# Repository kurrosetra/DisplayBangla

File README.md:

# DisplayBangla
INKA - Display for Bangladesh's train

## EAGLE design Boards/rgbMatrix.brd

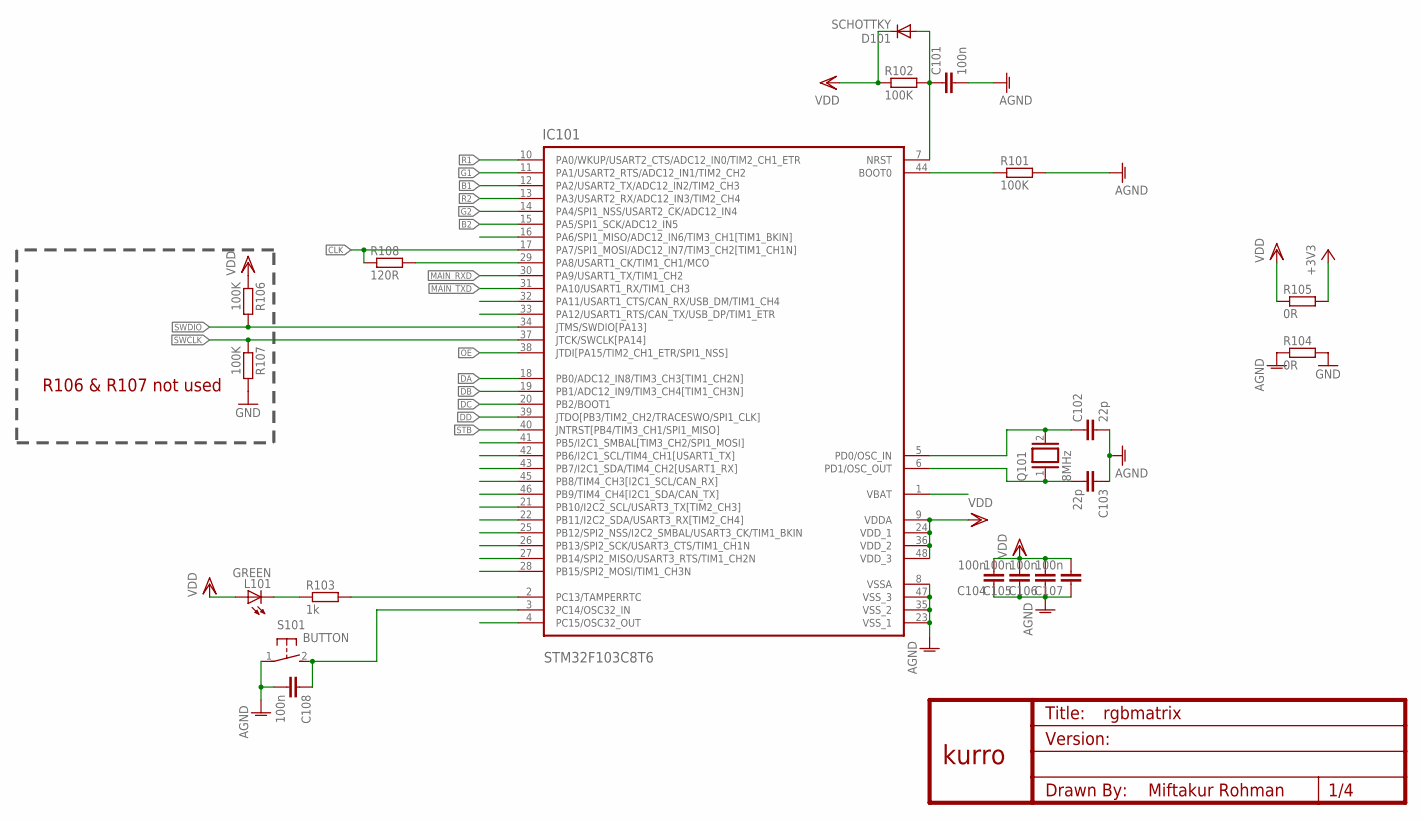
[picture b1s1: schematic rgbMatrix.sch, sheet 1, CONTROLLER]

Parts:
C101, C104, C105, C106, C107, C108: 100n; C0603
C102, C103: 22p; C0603
D101: SCHOTTKY; MICROMELF-W
IC101: STM32F103C8T6; QFP50P900X900X160-48N
L101: GREEN; LED3MM
Q101: 8MHz; QS
R101, R102, R106, R107: 100K; R0603
R103: 1k; R0603
R104, R105: 0R; R0603
R108: 120R; R0603
S101: BUTTON; B3F-01XXX
U$1: KURRO_FOOTPRINT; KURRO-LOGO

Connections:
+3V3: R105.2; also elsewhere on the board
AGND: C101.2, C102.2, C103.1, C104.1, C105.1, C106.1, C107.1, C108.2, IC101.8 (VSSA), IC101.23 (VSS_1), IC101.35 (VSS_2), IC101.47 (VSS_3), R101.2, R104.1, S101.1
B1: IC101.12 (PA2/USART2_TX/ADC12_IN2/TIM2_CH3); also elsewhere on the board
B2: IC101.15 (PA5/SPI1_SCK/ADC12_IN5); also elsewhere on the board
BOOT0: IC101.44 (BOOT0), R101.1
CLK: IC101.17 (PA7/SPI1_MOSI/ADC12_IN7/TIM3_CH2[TIM1_C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), R108.1; also elsewhere on the board
DA: IC101.18 (PB0/ADC12_IN8/TIM3_CH3[TIM1_CH2N]); also elsewhere on the board
DB: IC101.19 (PB1/ADC12_IN9/TIM3_CH4[TIM1_CH3N]); also elsewhere on the board
DC: IC101.20 (PB2/BOOT1); also elsewhere on the board
DD: IC101.39 (JTDO[PB3/TIM2_CH2/TRACESWO/SPI1_CLK]); also elsewhere on the board
G1: IC101.11 (PA1/USART2_RTS/ADC12_IN1/TIM2_CH2); also elsewhere on the board
G2: IC101.14 (PA4/SPI1_NSS/USART2_CK/ADC12_IN4); also elsewhere on the board
GND: R104.2, R107.2; also elsewhere on the board
LED1_BUILTIN: IC101.2 (PC13/TAMPERRTC), R103.2
MAIN_RXD: IC101.30 (PA9/USART1_TX/TIM1_CH2)
MAIN_TXD: IC101.31 (PA10/USART1_RX/TIM1_CH3); also elsewhere on the board
unnamed: IC101.29 (PA8/USART1_CK/TIM1_CH1/MCO), R108.2
unnamed: C103.2, IC101.6 (PD1/OSC_OUT), Q101.1
unnamed: C102.1, IC101.5 (PD0/OSC_IN), Q101.2
unnamed: L101.K (C), R103.1
unnamed: C108.1, IC101.3 (PC14/OSC32_IN), S101.2 (S)
OE: IC101.38 (JTDI[PA15/TIM2_CH1_ETR/SPI1_NSS]); also elsewhere on the board
R1: IC101.10 (PA0/WKUP/USART2_CTS/ADC12_IN0/TIM2_CH1_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); also elsewhere on the board
R2: IC101.13 (PA3/USART2_RX/ADC12_IN3/TIM2_CH4); also elsewhere on the board
RST: C101.1, D101.A, IC101.7 (NRST), R102.2
STB: IC101.40 (JNTRST[PB4/TIM3_CH1/SPI1_MISO]); also elsewhere on the board
SWCLK: IC101.37 (JTCK/SWCLK[PA14]), R107.1; also elsewhere on the board
SWDIO: IC101.34 (JTMS/SWDIO[PA13]), R106.2; also elsewhere on the board
VDD: C104.2, C105.2, C106.2, C107.2, D101.C, IC101.9 (VDDA), IC101.24 (VDD_1), IC101.36 (VDD_2), IC101.48 (VDD_3), L101.A, R102.1, R105.1, R106.1

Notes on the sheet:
R106 & R107 not used

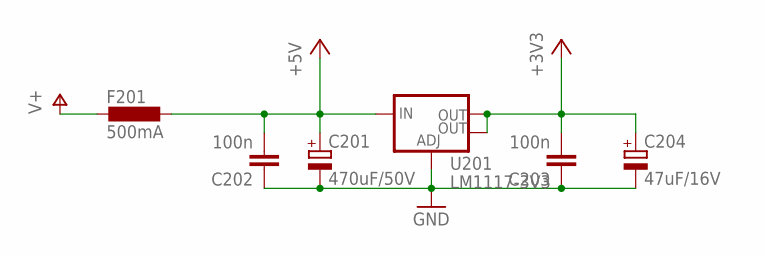
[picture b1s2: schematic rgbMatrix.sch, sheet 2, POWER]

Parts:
C201: 470uF/50V; E5-10,5
C202, C203: 100n; C0603
C204: 47uF/16V; E2-5
F201: 500mA; L1812
U201: LM1117-3V3; SOT223

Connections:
+3V3: C203.2, C204.+, U201.2 (OUT), U201.4 (OUT); also elsewhere on the board
+5V: C201.+, C202.2, F201.1, U201.3 (IN)
GND: C201.-, C202.1, C203.1, C204.-, U201.1 (ADJ); also elsewhere on the board
V+: F201.2; also elsewhere on the board

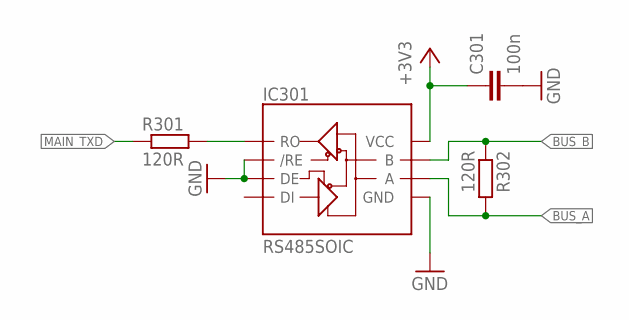
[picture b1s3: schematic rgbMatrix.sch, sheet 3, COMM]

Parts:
C301: 100n; C0603
IC301: RS485SOIC; SO08
R301, R302: 120R; R0603

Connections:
+3V3: C301.1, IC301.8 (VCC); also elsewhere on the board
BUS_A: IC301.6 (A), R302.2; also elsewhere on the board
BUS_B: IC301.7 (B), R302.1; also elsewhere on the board
GND: C301.2, IC301.2 (/RE), IC301.3 (DE), IC301.5 (GND); also elsewhere on the board
MAIN_TXD: R301.1; also elsewhere on the board
unnamed: IC301.1 (RO), R301.2

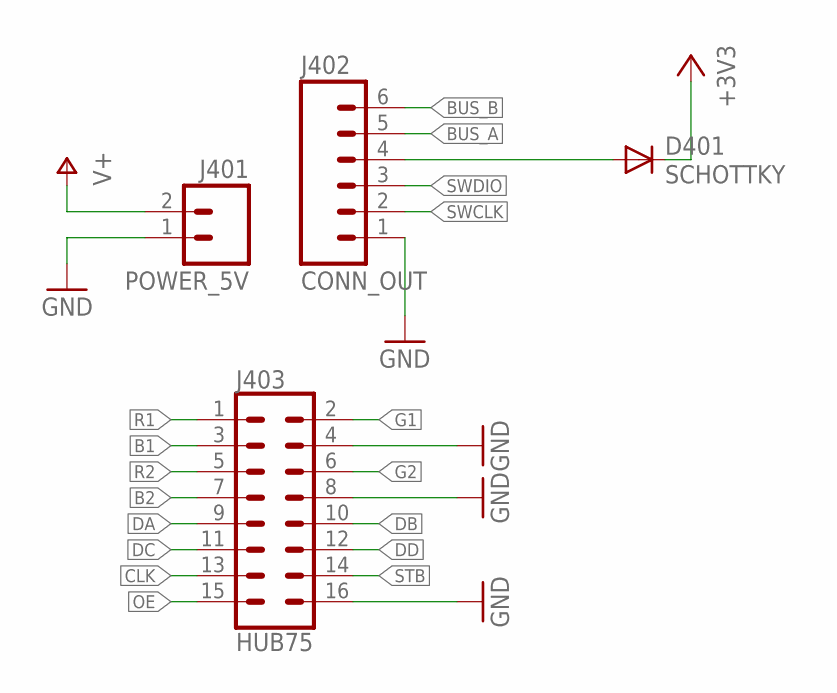
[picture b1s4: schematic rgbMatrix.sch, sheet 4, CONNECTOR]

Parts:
D401: SCHOTTKY; MICROMELF-W
J401: POWER_5V; XH-2-RA
J402: CONN_OUT; XH-6-RA
J403: HUB75; 2X08-LOCK

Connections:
+3V3: D401.C; also elsewhere on the board
B1: J403.3; also elsewhere on the board
B2: J403.7; also elsewhere on the board
BUS_A: J402.5; also elsewhere on the board
BUS_B: J402.6; also elsewhere on the board
CLK: J403.13; also elsewhere on the board
DA: J403.9; also elsewhere on the board
DB: J403.10; also elsewhere on the board
DC: J403.11; also elsewhere on the board
DD: J403.12; also elsewhere on the board
G1: J403.2; also elsewhere on the board
G2: J403.6; also elsewhere on the board
GND: J401.1, J402.1, J403.4, J403.8, J403.16; also elsewhere on the board
unnamed: D401.A, J402.4
OE: J403.15; also elsewhere on the board
R1: J403.1; also elsewhere on the board
R2: J403.5; also elsewhere on the board
STB: J403.14; also elsewhere on the board
SWCLK: J402.2; also elsewhere on the board
SWDIO: J402.3; also elsewhere on the board
V+: J401.2; also elsewhere on the board

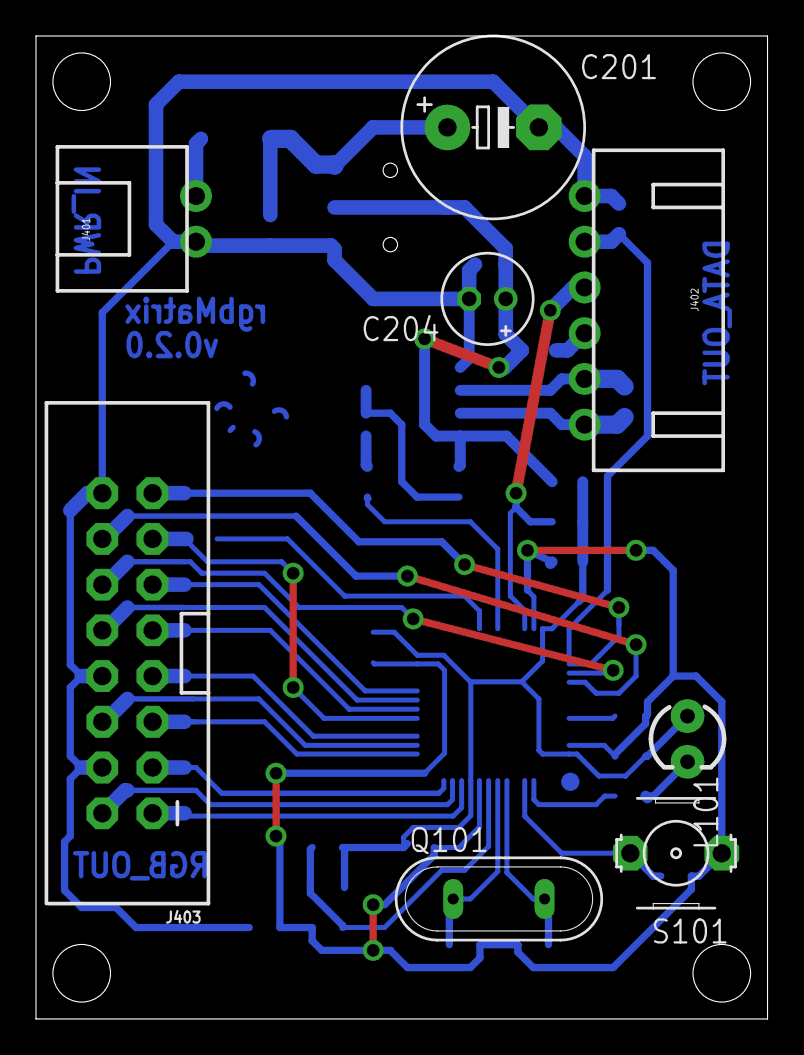
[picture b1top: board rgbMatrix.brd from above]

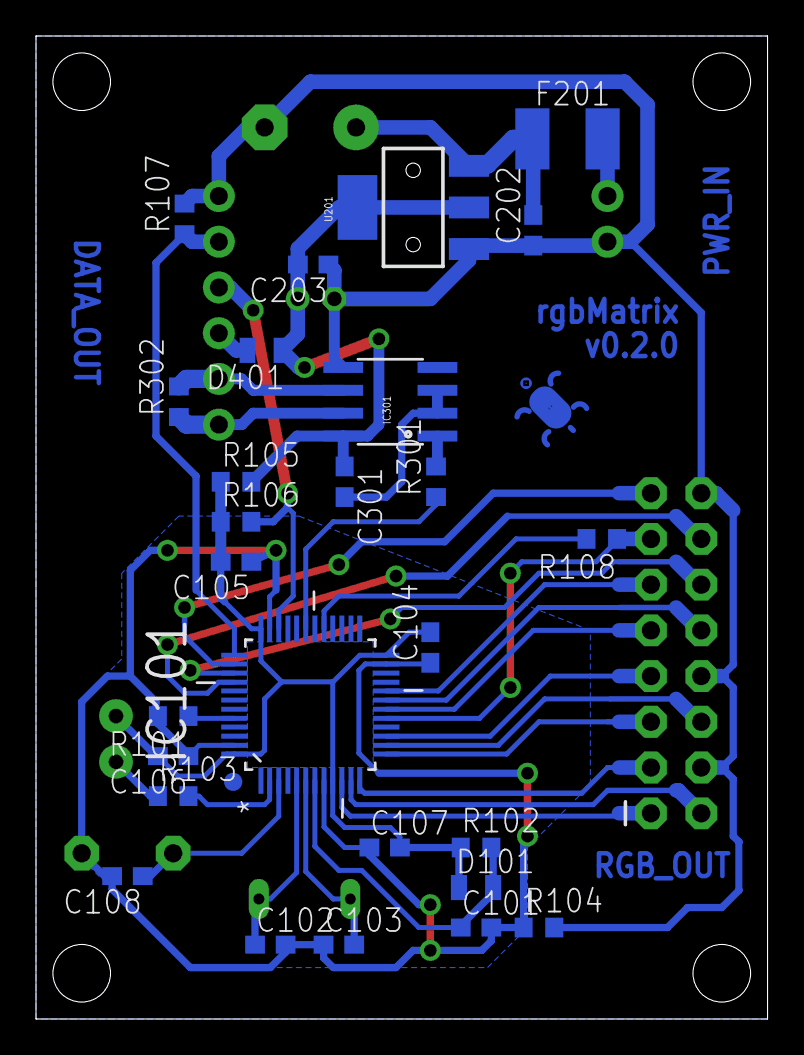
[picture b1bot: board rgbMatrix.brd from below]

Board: 2 copper layers, 40.6 x 54.6 mm, 36 parts (27 on the bottom side), 34 nets.

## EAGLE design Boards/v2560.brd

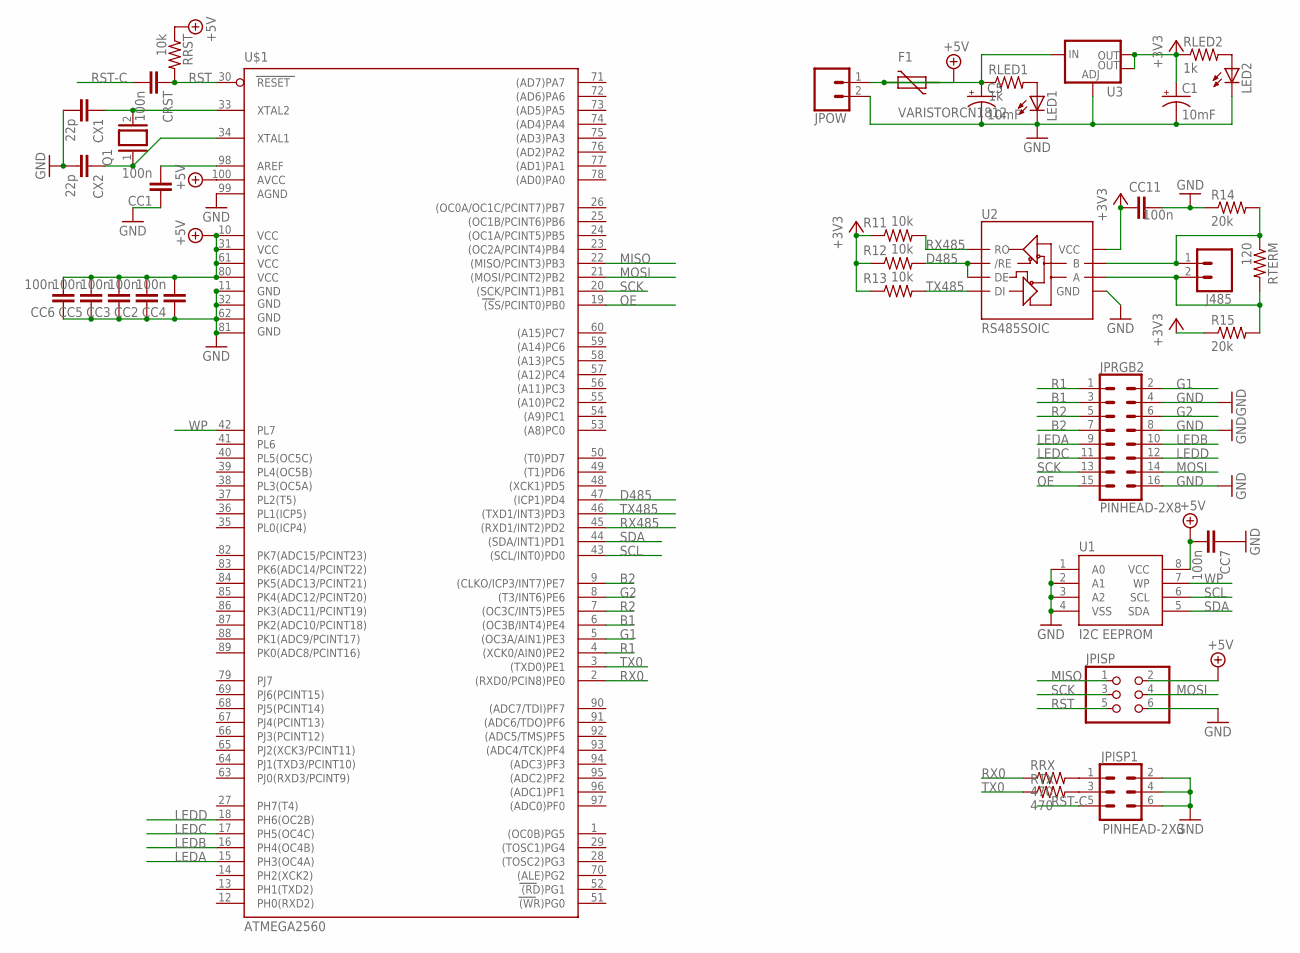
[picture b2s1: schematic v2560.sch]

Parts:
C1, C5: 10mF; CPOL-RADIAL-5MM-10MM
CC1, CC2, CC3, CC4, CC5, CC6, CC7, CC11: 100n; C0805
CRST: 100n; C0805
CX1, CX2: 22p; C0805
F1: VARISTORCN1812; CT/CN1812
J485: CONN_025MM; SCREWTERMINAL-5MM-2
JPISP: PINHD-2X3; 2X03
JPISP1: PINHEAD-2X3; 2X03-LOCK
JPOW: CONN_025MM; SCREWTERMINAL-5MM-2
JPRGB2: PINHEAD-2X8; 2X08-LOCK
LED1, LED2: LED3MM
Q1: XTAL/S; QS
R11, R12, R13: 10k; R0805
R14, R15: 20k; RES-0.3
RLED1, RLED2: 1k; R0805
RRST: 10k; R0805
RRX: 470; R0805
RTERM: 120; R0805
RTX: 470; R0805
U1: I2C EEPROM; SO08-EIAJ
U2: RS485SOIC; SO08
U3: V_REG_LM1117SOT223; SOT223
U$1: ATMEGA2560; TQFP100

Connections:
+3V3: C1.+, CC11.2, R11.1, R12.1, R13.1, R15.1, RLED2.1, U2.8 (VCC), U3.2 (OUT), U3.4 (OUT)
+5V: C5.+, CC2.2, CC3.2, CC4.2, CC5.2, CC6.2, CC7.2, F1.2, JPISP.2, RLED1.1, RRST.1, U1.8 (VCC), U3.3 (IN), U$1.10 (VCC), U$1.31 (VCC1), U$1.61 (VCC2), U$1.80 (VCC3), U$1.100 (AVCC)
AREF: CC1.2, U$1.98 (AREF)
B1: JPRGB2.3, U$1.6 ((OC3B/INT4)PE4)
B2: JPRGB2.7, U$1.9 ((CLKO/ICP3/INT7)PE7)
D485: R12.2, U2.2 (/RE), U2.3 (DE), U$1.47 ((ICP1)PD4)
G1: JPRGB2.2, U$1.5 ((OC3A/AIN1)PE3)
G2: JPRGB2.6, U$1.8 ((T3/INT6)PE6)
GND: C1.-, C5.-, CC1.1, CC2.1, CC3.1, CC4.1, CC5.1, CC6.1, CC7.1, CC11.1, CX1.2, CX2.2, JPISP.6, JPISP1.2, JPISP1.4, JPISP1.6, JPOW.2, JPRGB2.4, JPRGB2.8, JPRGB2.16, LED1.K (C), LED2.K (C), R14.1, U1.1 (A0), U1.2 (A1), U1.3 (A2), U1.4 (VSS), U2.5 (GND), U3.1 (ADJ), U$1.11 (GND), U$1.32 (GND1), U$1.62 (GND2), U$1.81 (GND3), U$1.99 (AGND)
LEDA: JPRGB2.9, U$1.15 (PH3(OC4A))
LEDB: JPRGB2.10, U$1.16 (PH4(OC4B))
LEDC: JPRGB2.11, U$1.17 (PH5(OC4C))
LEDD: JPRGB2.12, U$1.18 (PH6(OC2B))
MISO: JPISP.1, U$1.22 ((MISO/PCINT3)PB3)
MOSI: JPISP.4, JPRGB2.14, U$1.21 ((MOSI/PCINT2)PB2)
unnamed: J485.2, R15.2, RTERM.2, U2.6 (A)
unnamed: CX1.1, Q1.2, U$1.33 (XTAL2)
unnamed: CX2.1, Q1.1, U$1.34 (XTAL1)
unnamed: LED1.A, RLED1.2
unnamed: LED2.A, RLED2.2
unnamed: J485.1, R14.2, RTERM.1, U2.7 (B)
unnamed: F1.1, JPOW.1
unnamed: JPISP1.3, RTX.2
unnamed: JPISP1.1, RRX.2
OE: JPRGB2.15, U$1.19 ((SS/PCINT0)PB0)
R1: JPRGB2.1, U$1.4 ((XCK0/AIN0)PE2)
R2: JPRGB2.5, U$1.7 ((OC3C/INT5)PE5)
RST: CRST.1, JPISP.5, RRST.2, U$1.30 (RESET)
RST-C: CRST.2, JPISP1.5
RX0: RRX.1, U$1.2 ((RXD0/PCIN8)PE0)
RX485: R11.2, U2.1 (RO), U$1.45 ((RXD1/INT2)PD2)
SCK: JPISP.3, JPRGB2.13, U$1.20 ((SCK/PCINT1)PB1)
SCL: U1.6 (SCL), U$1.43 ((SCL/INT0)PD0)
SDA: U1.5 (SDA), U$1.44 ((SDA/INT1)PD1)
TX0: RTX.1, U$1.3 ((TXD0)PE1)
TX485: R13.2, U2.4 (DI), U$1.46 ((TXD1/INT3)PD3)
WP: U1.7 (WP), U$1.42 (PL7)

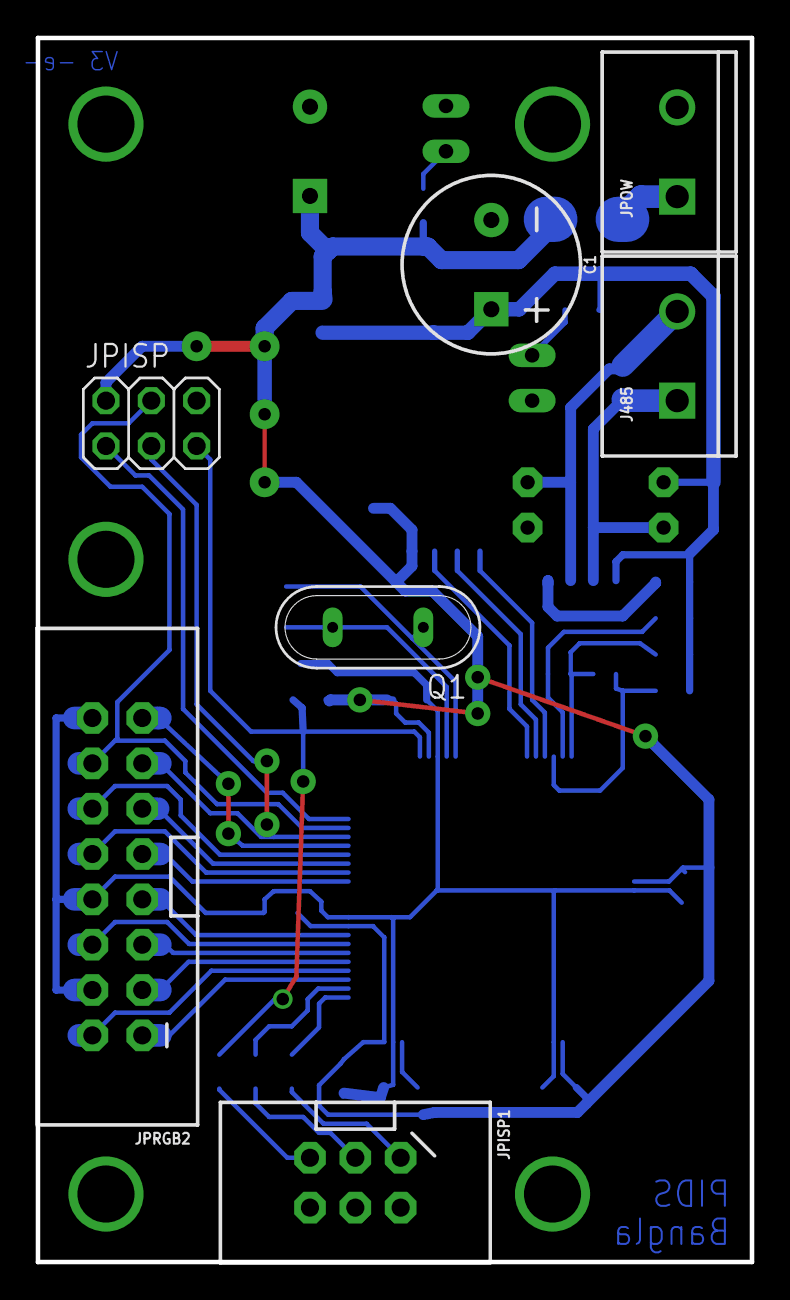
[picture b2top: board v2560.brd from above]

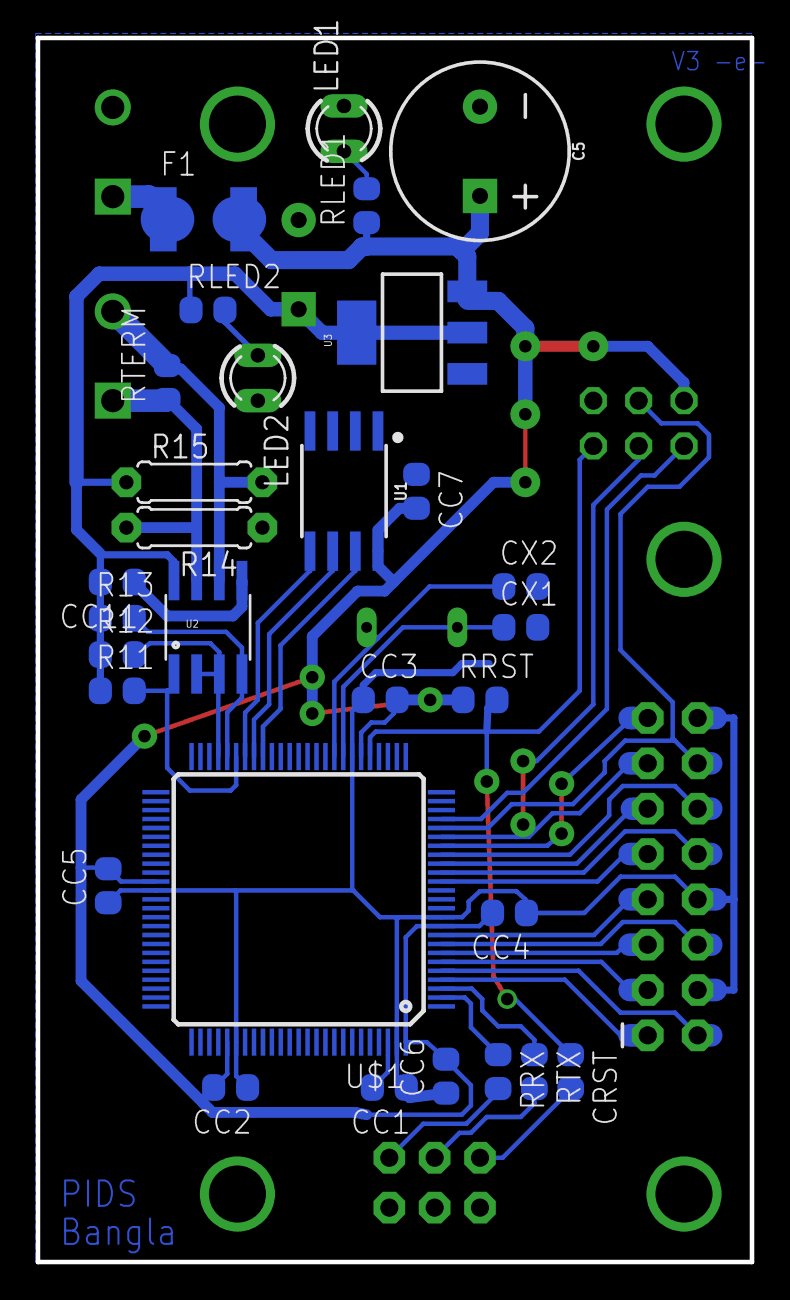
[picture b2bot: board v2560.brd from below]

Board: 2 copper layers, 40.0 x 68.6 mm, 37 parts (30 on the bottom side), 37 nets.

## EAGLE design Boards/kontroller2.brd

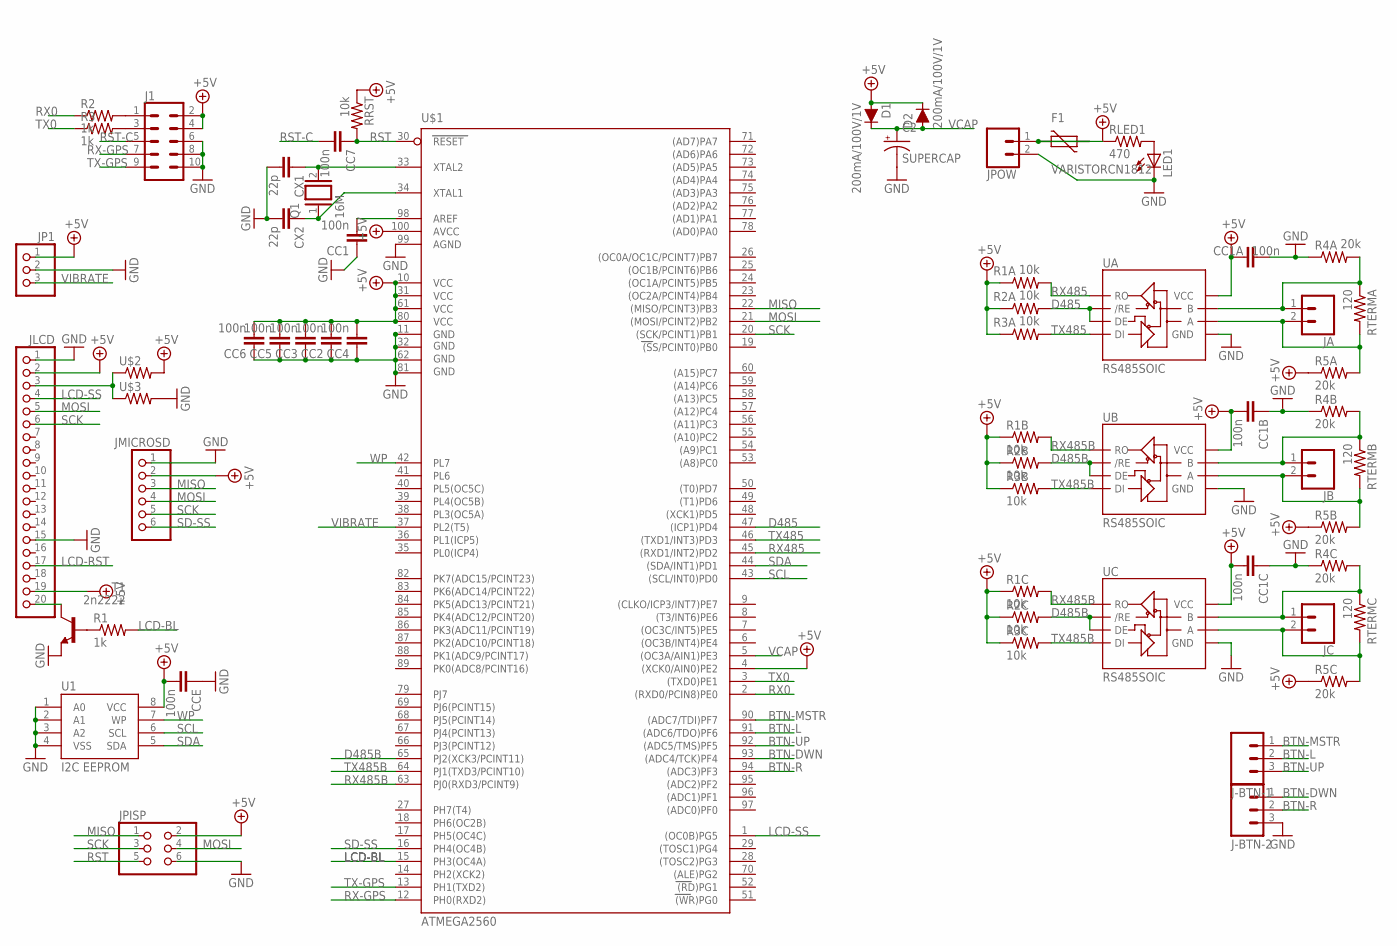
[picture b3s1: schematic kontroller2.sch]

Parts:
C2: SUPERCAP; SUPERCAP-25MM
CC1, CC1A, CC1B, CC1C, CC2, CC3, CC4, CC5, CC6, CC7: 100n; C0805
CCE: 100n; C0805
CX1, CX2: 22p; C0805
D1, D2: 200mA/100V/1V; DIODE-1N4148
F1: VARISTORCN1812; CT/CN1812
J1: CONN_05X2SHD_LOCK; 2X5-SHROUDED_LOCK
J-BTN-1, J-BTN-2: M03-SCREW-5MM; SCREWTERMINAL-5MM-3
JA: CONN_025MM; SCREWTERMINAL-5MM-2
JB: CONN_025MM; SCREWTERMINAL-5MM-2
JC: CONN_025MM; SCREWTERMINAL-5MM-2
JLCD: PINHD-1X20; 1X20
JMICROSD: PINHD-1X6; 1X06
JP1: PINHD-1X3; 1X03
JPISP: PINHD-2X3; 2X03
JPOW: CONN_025MM; SCREWTERMINAL-5MM-2
LED1: LED3MM
Q1: 16M; QS
R1, R2, R3: 1k; R0805
R1A, R1B, R1C, R2A, R2B, R2C, R3A, R3B, R3C: 10k; R0805
R4A, R4B, R4C, R5A, R5B, R5C: 20k; RES-0.3
RLED1: 470; R0805
RRST: 10k; R0805
RTERMA: 120; R0805
RTERMB: 120; R0805
RTERMC: 120; R0805
T1: 2n2222; TO92-EBC
U1: I2C EEPROM; SO08-EIAJ
U$1: ATMEGA2560; TQFP100
U$2, U$3: RES_R0805; R0805
UA: RS485SOIC; SO08
UB: RS485SOIC; SO08
UC: RS485SOIC; SO08

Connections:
+5V: CC1A.2, CC1B.2, CC1C.2, CC2.2, CC3.2, CC4.2, CC5.2, CC6.2, CCE.2, D1.A, D2.C, F1.2, J1.2, J1.4, JLCD.2, JLCD.19, JMICROSD.2, JP1.1, JPISP.2, R1A.1, R1B.1, R1C.1, R2A.1, R2B.1, R2C.1, R3A.1, R3B.1, R3C.1, R5A.1, R5B.1, R5C.1, RLED1.1, RRST.1, U1.8 (VCC), U$1.4 ((XCK0/AIN0)PE2), U$1.10 (VCC), U$1.31 (VCC1), U$1.61 (VCC2), U$1.80 (VCC3), U$1.100 (AVCC), U$2.2, UA.8 (VCC), UB.8 (VCC), UC.8 (VCC)
AREF: CC1.2, U$1.98 (AREF)
BTN-DWN: J-BTN-2.1, U$1.93 ((ADC4/TCK)PF4)
BTN-L: J-BTN-1.2, U$1.91 ((ADC6/TDO)PF6)
BTN-MSTR: J-BTN-1.1, U$1.90 ((ADC7/TDI)PF7)
BTN-R: J-BTN-2.2, U$1.94 ((ADC3)PF3)
BTN-UP: J-BTN-1.3, U$1.92 ((ADC5/TMS)PF5)
D485: R2A.2, U$1.47 ((ICP1)PD4), UA.2 (/RE), UA.3 (DE)
D485B: R2B.2, R2C.2, U$1.65 (PJ2(XCK3/PCINT11)), UB.2 (/RE), UB.3 (DE), UC.2 (/RE), UC.3 (DE)
GND: C2.-, CC1.1, CC1A.1, CC1B.1, CC1C.1, CC2.1, CC3.1, CC4.1, CC5.1, CC6.1, CCE.1, CX1.2, CX2.2, J1.6, J1.8, J1.10, J-BTN-2.3, JLCD.1, JLCD.15, JMICROSD.1, JP1.2, JPISP.6, JPOW.2, LED1.K (C), R4A.1, R4B.1, R4C.1, T1.E, U1.1 (A0), U1.2 (A1), U1.3 (A2), U1.4 (VSS), U$1.11 (GND), U$1.32 (GND1), U$1.62 (GND2), U$1.81 (GND3), U$1.99 (AGND), U$3.2, UA.5 (GND), UB.5 (GND), UC.5 (GND)
LCD-BL: R1.2, U$1.15 (PH3(OC4A))
LCD-RST: JLCD.17
LCD-SS: JLCD.4, U$1.1 ((OC0B)PG5)
MISO: JMICROSD.3, JPISP.1, U$1.22 ((MISO/PCINT3)PB3)
MOSI: JLCD.5, JMICROSD.4, JPISP.4, U$1.21 ((MOSI/PCINT2)PB2)
unnamed: JA.2, R5A.2, RTERMA.2, UA.6 (A)
unnamed: JC.1, R4C.2, RTERMC.1, UC.7 (B)
unnamed: JB.1, R4B.2, RTERMB.1, UB.7 (B)
unnamed: JB.2, R5B.2, RTERMB.2, UB.6 (A)
unnamed: CX1.1, Q1.2, U$1.33 (XTAL2)
unnamed: CX2.1, Q1.1, U$1.34 (XTAL1)
unnamed: LED1.A, RLED1.2
unnamed: JLCD.3, U$2.1, U$3.1
unnamed: JLCD.20, T1.C
unnamed: R1.1, T1.B
unnamed: J1.1, R2.2
unnamed: J1.3, R3.2
unnamed: F1.1, JPOW.1
unnamed: JC.2, R5C.2, RTERMC.2, UC.6 (A)
unnamed: JA.1, R4A.2, RTERMA.1, UA.7 (B)
RST: CC7.1, JPISP.5, RRST.2, U$1.30 (RESET)
RST-C: CC7.2, J1.5
RX0: R2.1, U$1.2 ((RXD0/PCIN8)PE0)
RX485: R1A.2, U$1.45 ((RXD1/INT2)PD2), UA.1 (RO)
RX485B: R1B.2, R1C.2, U$1.63 (PJ0(RXD3/PCINT9)), UB.1 (RO), UC.1 (RO)
RX-GPS: J1.7, U$1.12 (PH0(RXD2))
SCK: JLCD.6, JMICROSD.5, JPISP.3, U$1.20 ((SCK/PCINT1)PB1)
SCL: U1.6 (SCL), U$1.43 ((SCL/INT0)PD0)
SD-SS: JMICROSD.6, U$1.16 (PH4(OC4B))
SDA: U1.5 (SDA), U$1.44 ((SDA/INT1)PD1)
TX0: R3.1, U$1.3 ((TXD0)PE1)
TX485: R3A.2, U$1.46 ((TXD1/INT3)PD3), UA.4 (DI)
TX485B: R3B.2, R3C.2, U$1.64 (PJ1(TXD3/PCINT10)), UB.4 (DI), UC.4 (DI)
TX-GPS: J1.9, U$1.13 (PH1(TXD2))
VCAP: C2.+, D1.C, D2.A, U$1.5 ((OC3A/AIN1)PE3)
VIBRATE: JP1.3, U$1.37 (PL2(T5))
WP: U1.7 (WP), U$1.42 (PL7)

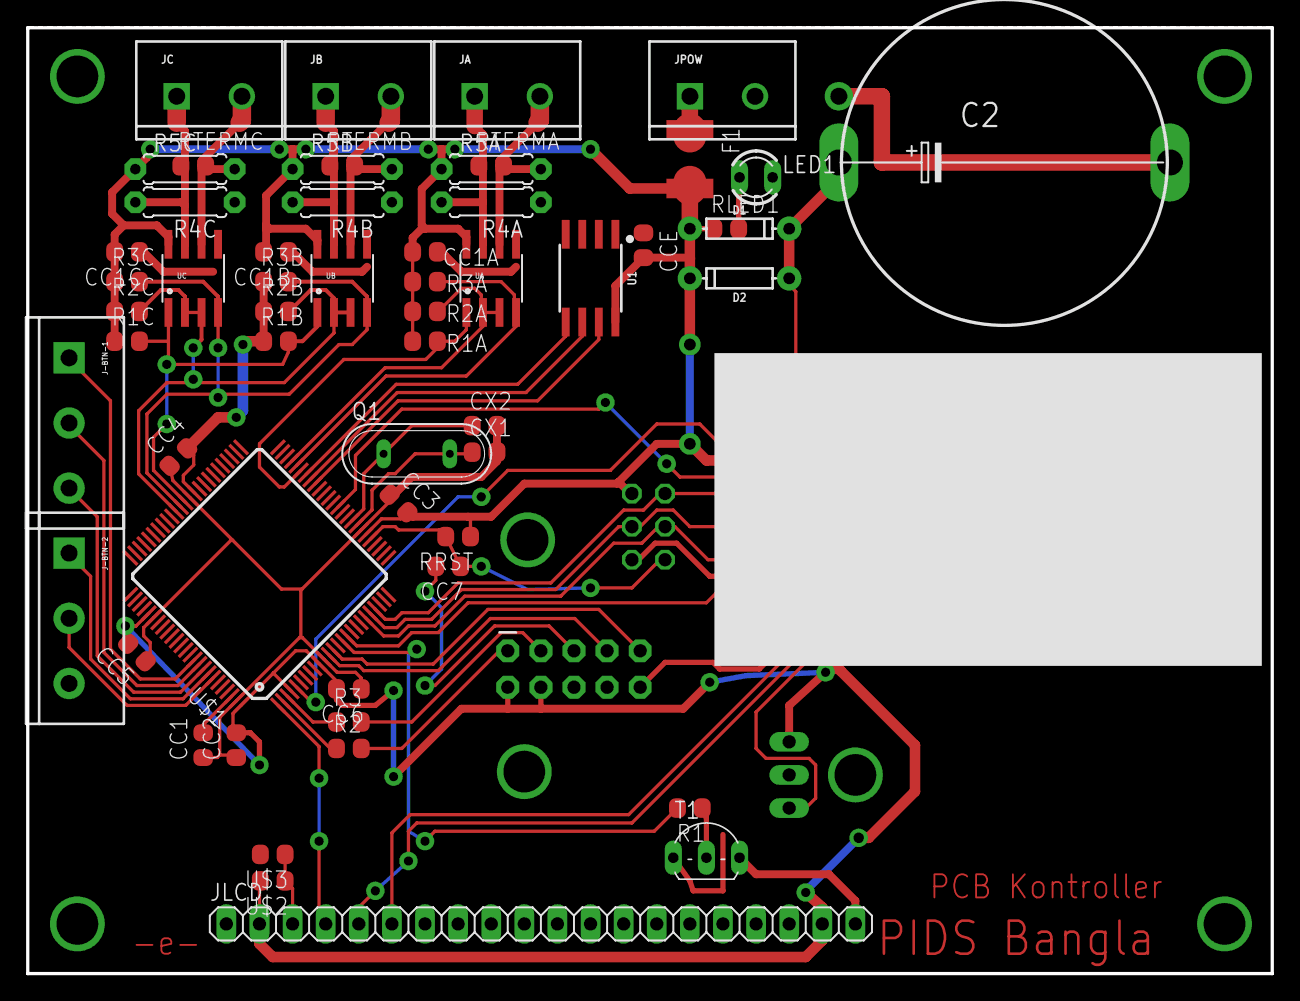
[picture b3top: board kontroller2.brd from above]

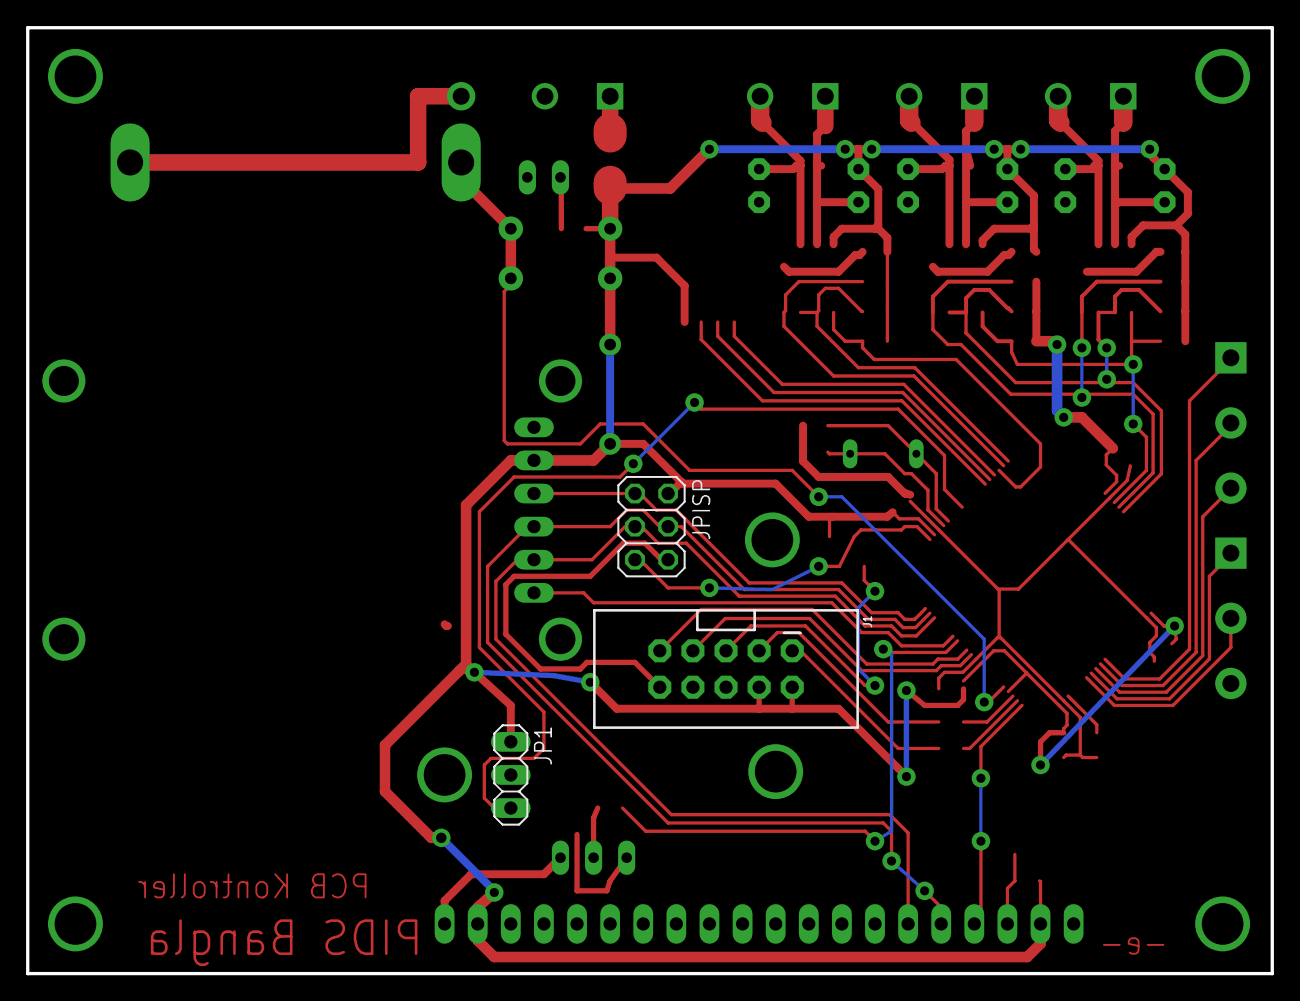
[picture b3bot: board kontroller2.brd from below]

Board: 2 copper layers, 95.5 x 72.6 mm, 61 parts (3 on the bottom side), 46 nets.

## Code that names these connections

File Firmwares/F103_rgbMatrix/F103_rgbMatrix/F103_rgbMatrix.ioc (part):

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Mcu.Name=STM32F103C(8-B)Tx
Mcu.Package=LQFP48
Mcu.UserName=STM32F103C8Tx
PA0-WKUP.GPIOParameters=GPIO_Speed,GPIO_Label
PA0-WKUP.GPIO_Label=r1
PA0-WKUP.GPIO_Speed=GPIO_SPEED_FREQ_HIGH
PA0-WKUP.Signal=GPIO_Output
PA1.GPIOParameters=GPIO_Speed,GPIO_Label
PA1.GPIO_Label=g1
PA1.GPIO_Speed=GPIO_SPEED_FREQ_HIGH
PA1.Signal=GPIO_Output
PA10.Mode=Asynchronous
PA10.Signal=USART1_RX
PA13.Mode=Serial_Wire
PA13.Signal=SYS_JTMS-SWDIO
PA14.Mode=Serial_Wire
PA14.Signal=SYS_JTCK-SWCLK
PA15.GPIOParameters=GPIO_Label
PA15.GPIO_Label=oe
PA15.Signal=GPIO_Output
PA2.GPIOParameters=GPIO_Speed,GPIO_Label
PA2.GPIO_Label=b1
PA2.GPIO_Speed=GPIO_SPEED_FREQ_HIGH
PA2.Signal=GPIO_Output
PA3.GPIOParameters=GPIO_Speed,GPIO_Label
PA3.GPIO_Label=r2
PA3.GPIO_Speed=GPIO_SPEED_FREQ_HIGH
PA3.Signal=GPIO_Output
PA4.GPIOParameters=GPIO_Speed,GPIO_Label
PA4.GPIO_Label=g2
PA4.GPIO_Speed=GPIO_SPEED_FREQ_HIGH
PA4.Signal=GPIO_Output
PA5.GPIOParameters=GPIO_Speed,GPIO_Label
PA5.GPIO_Label=b2
PA5.GPIO_Speed=GPIO_SPEED_FREQ_HIGH
PA5.Signal=GPIO_Output
PA7.GPIOParameters=GPIO_Speed,GPIO_PuPd,GPIO_Label,GPIO_ModeDefaultOutputPP
PA7.GPIO_Label=clk
PA7.GPIO_ModeDefaultOutputPP=GPIO_MODE_OUTPUT_PP
PA7.GPIO_PuPd=GPIO_NOPULL
PA7.GPIO_Speed=GPIO_SPEED_FREQ_HIGH
PA7.Signal=GPIO_Output
PA9.Mode=Asynchronous
PA9.Signal=USART1_TX
PB0.GPIOParameters=GPIO_Speed,GPIO_Label
PB0.GPIO_Label=da
PB0.GPIO_Speed=GPIO_SPEED_FREQ_HIGH
PB0.Signal=GPIO_Output
PB1.GPIOParameters=GPIO_Speed,GPIO_Label
PB1.GPIO_Label=db
PB1.GPIO_Speed=GPIO_SPEED_FREQ_HIGH
PB1.Signal=GPIO_Output
PB2.GPIOParameters=GPIO_Speed,GPIO_Label
PB2.GPIO_Label=dc
PB2.GPIO_Speed=GPIO_SPEED_FREQ_HIGH
PB2.Signal=GPIO_Output
PB3.GPIOParameters=GPIO_Speed,GPIO_Label
PB3.GPIO_Label=dd
PB3.GPIO_Speed=GPIO_SPEED_FREQ_HIGH
PB3.Signal=GPIO_Output
PB4.GPIOParameters=GPIO_Speed,GPIO_Label
PB4.GPIO_Label=stb
PB4.GPIO_Speed=GPIO_SPEED_FREQ_HIGH
PB4.Signal=GPIO_Output
PC13-TAMPER-RTC.GPIOParameters=GPIO_Speed,PinState,GPIO_Label
PC13-TAMPER-RTC.GPIO_Label=LED_BUILTIN
PC13-TAMPER-RTC.GPIO_Speed=GPIO_SPEED_FREQ_HIGH
PC13-TAMPER-RTC.PinState=GPIO_PIN_SET
PC13-TAMPER-RTC.Signal=GPIO_Output
PD0-OSC_IN.Mode=HSE-External-Oscillator
PD0-OSC_IN.Signal=RCC_OSC_IN
PD1-OSC_OUT.Mode=HSE-External-Oscillator
PD1-OSC_OUT.Signal=RCC_OSC_OUT
RCC.SYSCLKFreq_VALUE=72000000
RCC.SYSCLKSource=RCC_SYSCLKSOURCE_PLLCLK
board=custom

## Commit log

2018-03-16 Init Brainstorming
2018-03-19 initial commit
    uncomplete firmware
2018-03-22 update
    - add example pid files
    - downgrade u8g2 library to u8g
    - add main page
    - add menu page (incomplete)
2018-03-23 delete menuDisplay class
    due to simplicity of transfer data button, lcd & sd card
2018-03-23 update
    - not using default.txt
2018-03-23 update pageSubMenu
    working submenu:
    - train route
    - language
    - master mode
    - gps mode
2018-03-26 update current station submenu page
2018-03-27 update
    - delete "DEFAULT.txt" as temporary train info holder, train info will be search straight within SD
    - create trainDetal.h that contain Train_Detail struct due to eclipse sloeber limitation when using function with struct as parameter
    - change sdUpdateTrainDetail() function to sdUpdateTrainDetail(Train_Detail *td)
    - change station menu according to trainRoute option
    - each time trainRoute option's changed, currentStationPosition & currentStationName will be updated as well
2018-03-27 update
    Major:
    - add trainName pageSubMenu
    Minor:
    - change trainDetal.h to trainDetail.h (typo)
2018-03-28 add coach pageSubMenu
2018-03-28 create storageBank library
    usage: to store and load repetitive block of data (ex. setting or config) to eeprom
2018-04-02 fix storageBank
    previous:
    each full cycles, block header update 5x
    update:
    each full cycles, block header update 1x
2018-04-02 Implements storageBank library
2018-04-03 Implement comm function
    v0.2.0
2018-04-17 hotfix
    fix:
    if coach.txt in the middle/ not in first line
2018-04-17 Revert "Implement comm function"
    This reverts commit 3894bb4b592562701d81fb088c44ee22dd204580.
2018-04-17 Revert "hotfix"
    This reverts commit 09f8be90277431a554eb64818dcf1b734301ec4b.
2018-04-17 update hotfix-2
    add exception when end of line of the last line of file isnt '\n'
2018-07-13 v20180714
2018-07-23 beta release
2018-07-23 adding library u8g for lcd
2018-07-23 Revert "adding library u8g for lcd"
    This reverts commit eb5ddd7eb6f6b827ffd762f3ad1e75b023514e03.
2018-08-14 1.1.0
    add bangla font
2018-08-18 v1.2.0
    add:
    - gps function
    - libraries
2018-08-19 1.2.0b
    add coordinate to pid file
2018-09-07 1.2.1
    hotfix:
    1. busparsing fixed
    2. start masterUpdateTrainBangla() when buttonUpdate
2018-09-11 v1.3.0
    MAJOR UPDATE:
    add Display module with stm32f103c8t6
    todo list:
    1. parsing command
    2. layout
2018-09-14 v1.3.1
    MINOR UPDATE:
    add parsing functions
    todo list:
    1. layout
    2. add swapbuffer
2018-09-14 v1.3.2
    MINOR UPDATE:
    add swapbuffer
    todo list:
    1. layout
2018-09-14 v1.3.3
    MINOR UPDATE:
    layout:
    1. english & bangla
    todo:
    1. bintik2, ganti ke dma mem_to_mem?
2018-09-17 v1.3.4
    test dma
2018-09-17 Revert "Dev firmware"
2018-09-17 v1.3.4
    HOTFIX UPDATE:
    1. dma from timer compare to timer update
    todo:
    1. layout animation
2018-09-17 v1.3.5
    MINOR UPDATE:
    layout:
    1. running text animation (outdoor)
    todo:
    1. running text animation (indoor)
2018-09-18 v1.3.6
    FIX UPDATE:
    1. layout Outdoor & Indoor
    2. create HEX binaries files
2018-09-19 v1.3.6b
    FIX UPDATE:
    1. all red color
    2. slower running speed
2018-09-20 v1.3.6c
    FIX UPDATE:
    1. fix serial data sequence (coachName)
    2. indoor: fix trainRoute in bangla (eliminate unwanted space)
    3. outdoor: fix trainRoute in english&bangla (running animation bug)
2018-09-24 v1.3.6c2
    FIX UPDATE:
    1. Outdoor bangla layoutTrainName constrain from "xTrainIdLineEnd" change to "xCoachLineEnd"
2018-09-24 v1.3.7
    MINOR UPDATE:
    1. GPS function tested
    2. coachName space char fixed
2018-10-05 v1.3.8
    MINOR UPDATE:
    1. kontroller:
    a. update hardware
    b. change pinout in software
    2. display:
    a. add ring buffer to capture serial command (no glitch anymore
2018-10-09 v1.3.8a
    FIX UPDATE:
    1. Display Module:
    a. set brightness level of INDOOR display from 20% to 50%
    2. Kontroller Module:
    a. available for v3 & v3a
2018-10-09 v1.3.8b
    FIX UPDATE:
    1. Display Module:
    a. lengthening DISPLAY_REFRESH_TIMEOUT from 10s to 30s to accomodate longer string to be displayed.
2018-10-10 v.1.3.8c
    FIX Update:
    1. support controller v3 & v3a (previously different pinout in schematic of controller v3)
2019-09-05 v1.5.0
    Changelog v1.5.0:
    - [MAJOR] support outdoor module with new IC led driver (ICN2308S) that need 3 clock when LATCH HIGH
    - [MAJOR] change timing control for display module
    v1.3.9, v1.4.0 & 1.4.1 from edes:
    change in v.1.4.1:
    - corrected display of Coach-ID if 4-digit is assigned
2019-10-26 v1.5.1
    Changelog v1.5.1:
    - [MINOR] support new outdoor module display which is different in pixel mapping
2020-11-02 update font tambahan
    ada char yang salah
    -e- updated edes 31Okt2020
2020-11-02 update hex untuk indoor & outdoor

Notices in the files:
parts and their libraries:
SparkFun-Connectors: Licensing: Creative Commons ShareAlike 4.0 International - https://creativecommons.org/licenses/by-sa/4.0
SparkFun-Connectors: Licensing: CC v3.0 Share-Alike You are welcome to use this library for commercial purposes.
